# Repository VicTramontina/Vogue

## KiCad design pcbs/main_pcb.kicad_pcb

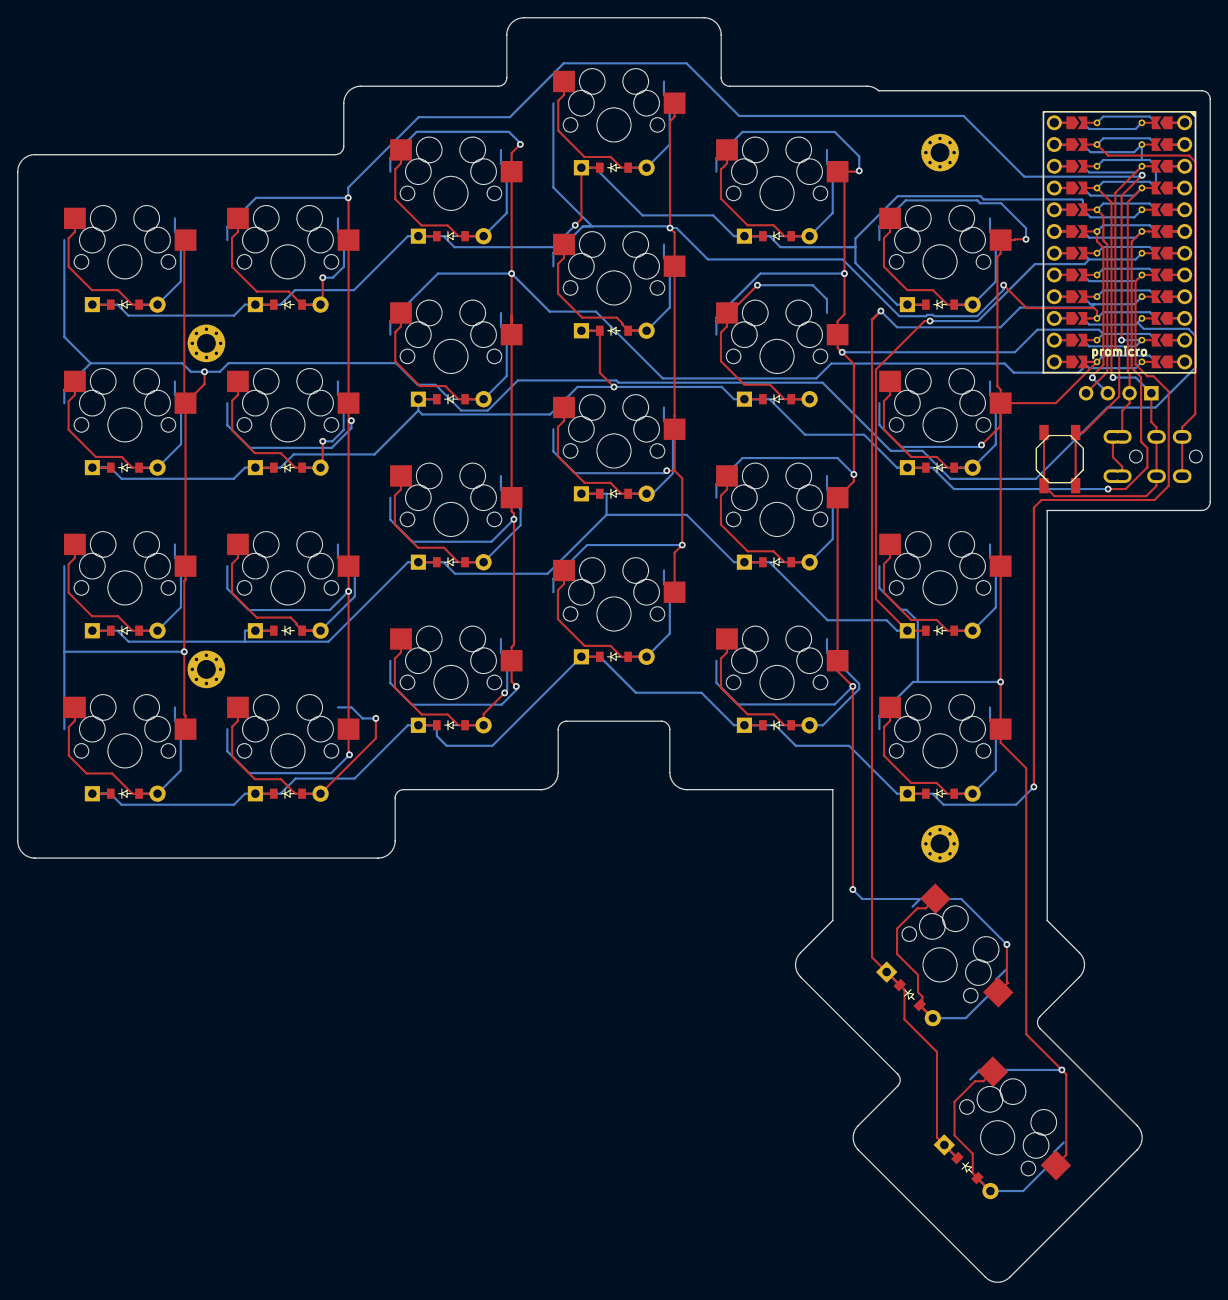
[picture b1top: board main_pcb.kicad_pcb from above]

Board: 2 copper layers, 139.3 x 147.8 mm, 60 parts (0 on the bottom side), 43 nets.

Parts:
B1: SW_TACT_ALPS_SKQGABE010
D1, D2, D3, D4, D5, D6, D7, D8, D9, D10, D11, D12, D13, D14, D15, D16, D17, D18, D19, D20, D21, D22, D23, D24, D25, D26: ComboDiode
MCU1: nice!nano_v2
OLED1: OLED; OLED_headers
S1, S2, S3, S4, S5, S6, S7, S8, S9, S10, S11, S12, S13, S14, S15, S16, S17, S18, S19, S20, S21, S22, S23, S24, S25, S26: MX
TRRS1: TRRS-PJ-320A-dual
_1, _2, _3, _4: MountingHole_2.2mm_M2_Pad_Via

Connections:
GND: B1.1, MCU1.GND, OLED1.1, TRRS1.3
P0: MCU1.P0, TRRS1.4
P2: MCU1.P2, OLED1.4
P3: MCU1.P3, OLED1.3
P7: MCU1.P7, S13.1, S14.1, S15.1, S16.1
P8: MCU1.P8, S17.1, S18.1, S19.1, S20.1, S25.1
P9: MCU1.P9, S21.1, S22.1, S23.1, S24.1, S26.1
P10: MCU1.P10, S9.1, S10.1, S11.1, S12.1
P14: MCU1.P14, S1.1, S2.1, S3.1, S4.1
P15: D25.1, D26.1, MCU1.P15
P16: MCU1.P16, S5.1, S6.1, S7.1, S8.1
P18: D1.1, D5.1, D9.1, D13.1, D17.1, D21.1, MCU1.P18
P19: D2.1, D6.1, D10.1, D14.1, D18.1, D22.1, MCU1.P19
P20: D3.1, D7.1, D11.1, D15.1, D19.1, D23.1, MCU1.P20
P21: D4.1, D8.1, D12.1, D16.1, D20.1, D24.1, MCU1.P21
RST: B1.2, MCU1.RST
VCC: MCU1.VCC, OLED1.2, TRRS1.1, TRRS1.2
aditional_bottom: D21.2, S21.2
aditional_home: D22.2, S22.2
aditional_num: D23.2, S23.2
aditional_top: D24.2, S24.2
index_bottom: D13.2, S13.2
index_home: D14.2, S14.2
index_num: D15.2, S15.2
index_top: D16.2, S16.2
inner_bottom: D17.2, S17.2
inner_home: D18.2, S18.2
inner_num: D19.2, S19.2
inner_top: D20.2, S20.2
middle_bottom: D9.2, S9.2
middle_home: D10.2, S10.2
middle_num: D11.2, S11.2
middle_top: D12.2, S12.2
one_main: D25.2, S25.2
pinky_bottom: D1.2, S1.2
pinky_home: D2.2, S2.2
pinky_num: D3.2, S3.2
pinky_top: D4.2, S4.2
ring_bottom: D5.2, S5.2
ring_home: D6.2, S6.2
ring_num: D7.2, S7.2
ring_top: D8.2, S8.2
two_main: D26.2, S26.2

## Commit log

2025-07-31 gerbers
2026-03-17 Add EE_HANDS definition and update keyboard matrix configuration
2026-04-22 Add VIA_ENABLE variable to rules.mk
